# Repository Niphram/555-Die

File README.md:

# 555 Die

Small kit I designed for my brother, may be interesting to some.
Designed using KiCAD 5.

## Parts

| Designator       |               Value |          Package           |
| ---------------- | ------------------: | :------------------------: |
| R13 - R16        |                 1kΩ |       Axial DIN0207        |
| R2, R3, R5 - R12 |                10kΩ |       Axial DIN0207        |
| R1, R4           |               4.7MΩ |       Axial DIN0207        |
| D1 - D7          |                 LED |            5mm             |
| Q1, Q3           |               BC557 |           TO-92            |
| Q2, Q4, Q5       |               BC647 |           TO-92            |
| C1               |               0.1μF | Disc D5.0mm W2.5mm P2.50mm |
| C2               |                 1μF |    Radial D5.0mm P2.5mm    |
| SW1              |         Tact Switch |            6mm             |
| U1               |               NE555 |  DIP-8 (Optional Socket)   |
| U2               |              CD4017 |  DIP-16 (Optional Socket)  |
| BT1              | Powersource (3V-9V) |

> R4 and R1 can be changed to alter timings.

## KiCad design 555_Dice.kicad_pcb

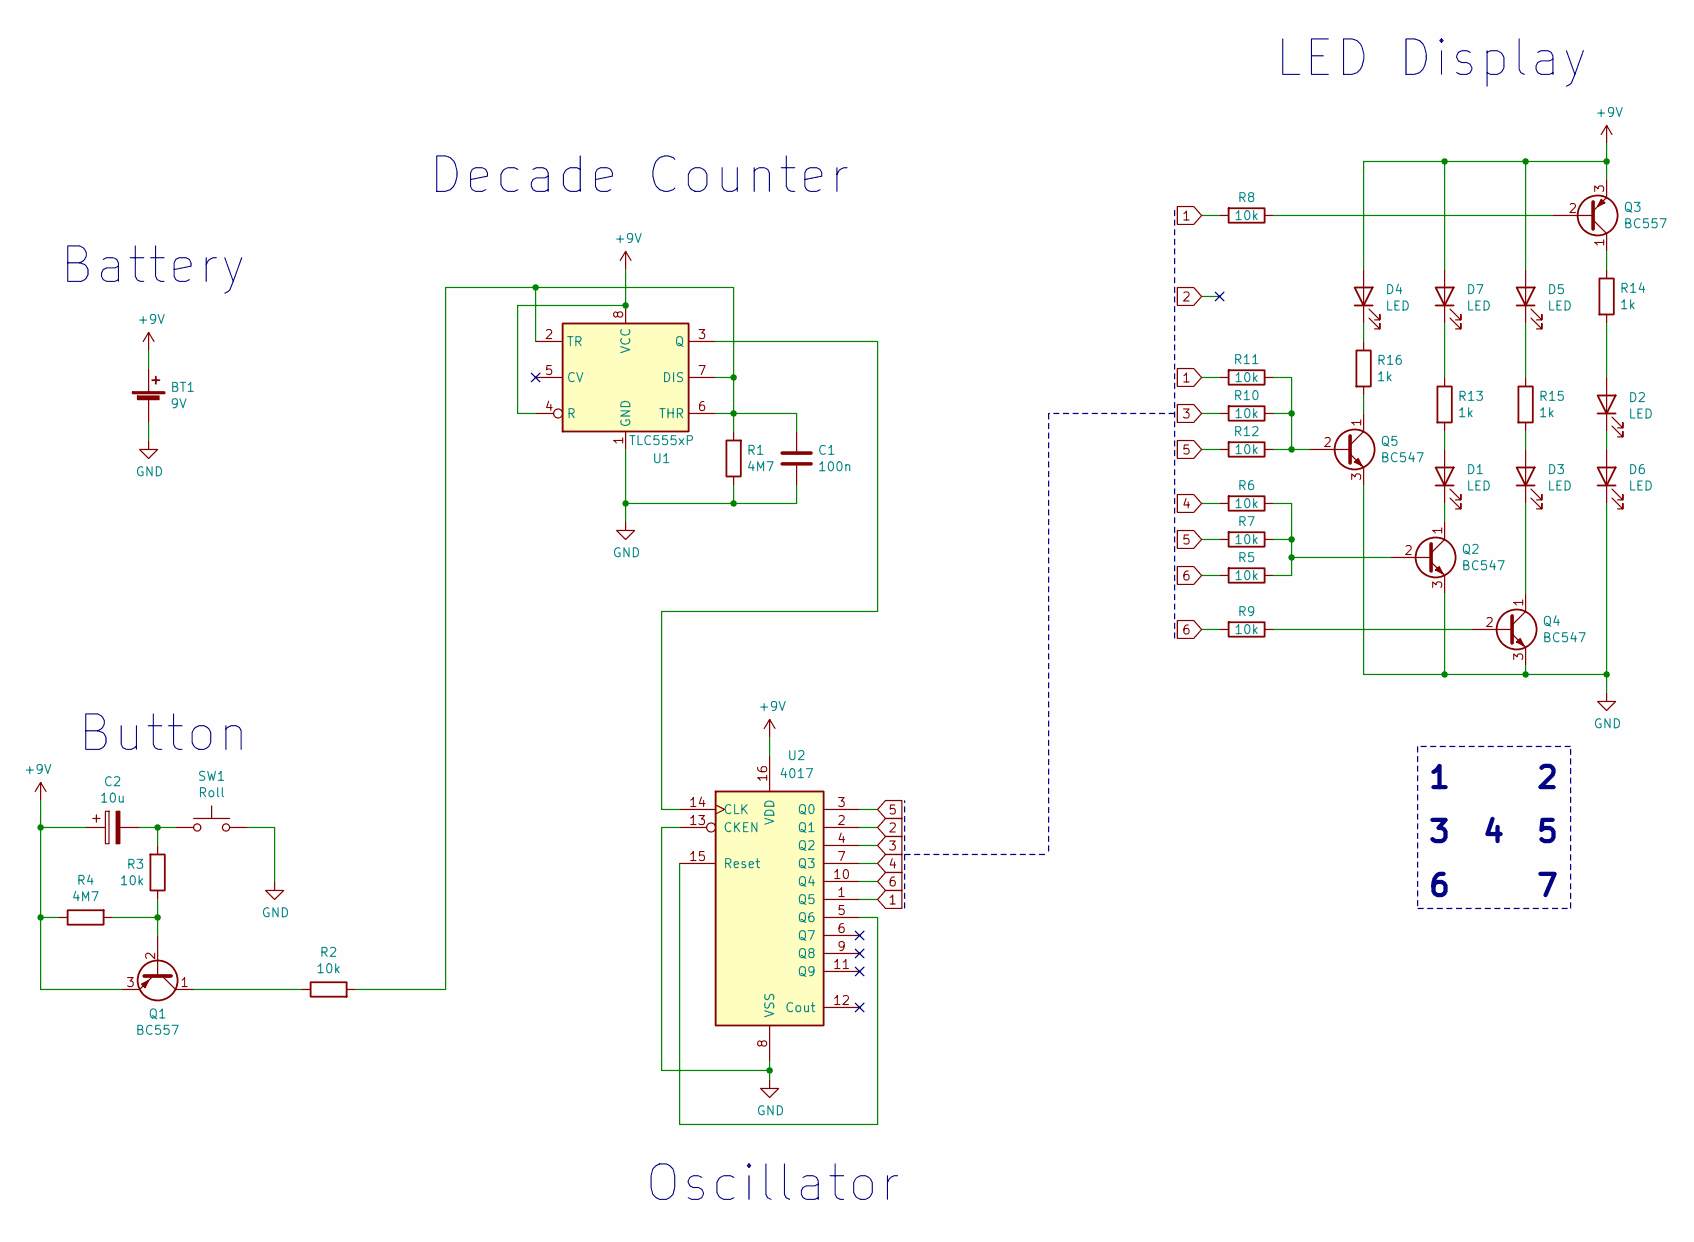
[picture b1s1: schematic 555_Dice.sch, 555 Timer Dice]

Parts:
BT1: 9V; TerminalBlock_bornier-2_P5.08mm
C1: 100n; C_Disc_D5.0mm_W2.5mm_P2.50mm
C2: 10u; CP_Radial_D5.0mm_P2.50mm
D1, D2, D3, D4, D5, D6, D7: LED; LED_D5.0mm
Q1, Q3: BC557; TO-92_HandSolder
Q2, Q4, Q5: BC547; TO-92_HandSolder
R1, R4: 4M7; R_Axial_DIN0207_L6.3mm_D2.5mm_P10.16mm_Horizontal
R2, R3, R5, R6, R7, R8, R9, R10, R11, R12: 10k; R_Axial_DIN0207_L6.3mm_D2.5mm_P10.16mm_Horizontal
R13, R14, R15, R16: 1k; R_Axial_DIN0207_L6.3mm_D2.5mm_P10.16mm_Horizontal
SW1: Roll; SW_PUSH_6mm_H4.3mm
U1: TLC555xP; DIP-8_W7.62mm_Socket_LongPads
U2: 4017; DIP-16_W7.62mm_Socket_LongPads

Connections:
1: R8.2, R11.2, U2.1 (Q5)
2: U2.2 (Q1)
3: R10.2, U2.4 (Q2)
4: R6.2, U2.7 (Q3)
5: R7.2, R12.2, U2.3 (Q0)
6: R5.2, R9.2, U2.10 (Q4)
+9V: BT1.1 (+), C2.1, D4.2 (A), D5.2 (A), D7.2 (A), Q1.3 (E), Q3.3 (E), R4.1, U1.4 (R), U1.8 (VCC), U2.16 (VDD)
GND: BT1.2 (-), C1.2, D6.1 (K), Q2.3 (E), Q4.3 (E), Q5.3 (E), R1.1, SW1.1, U1.1 (GND), U2.8 (VSS), U2.13 (CKEN)
unnamed: C1.1, R1.2, R2.2, U1.2 (TR), U1.6 (THR), U1.7 (DIS)
unnamed: C2.2, R3.2, SW1.2
unnamed: D1.1 (K), Q2.1 (C)
unnamed: D1.2 (A), R13.2
unnamed: D2.1 (K), D6.2 (A)
unnamed: D2.2 (A), R14.2
unnamed: D3.1 (K), Q4.1 (C)
unnamed: D3.2 (A), R15.2
unnamed: D4.1 (K), R16.1
unnamed: D5.1 (K), R15.1
unnamed: D7.1 (K), R13.1
unnamed: Q1.1 (C), R2.1
unnamed: Q1.2 (B), R3.1, R4.2
unnamed: Q2.2 (B), R5.1, R6.1, R7.1
unnamed: Q3.1 (C), R14.1
unnamed: Q3.2 (B), R8.1
unnamed: Q4.2 (B), R9.1
unnamed: Q5.1 (C), R16.2
unnamed: Q5.2 (B), R10.1, R11.1, R12.1
unnamed: U1.3 (Q), U2.14 (CLK)
unnamed: U2.5 (Q6), U2.15 (Reset)

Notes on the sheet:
Battery
Button
Oscillator
Decade Counter
LED Display

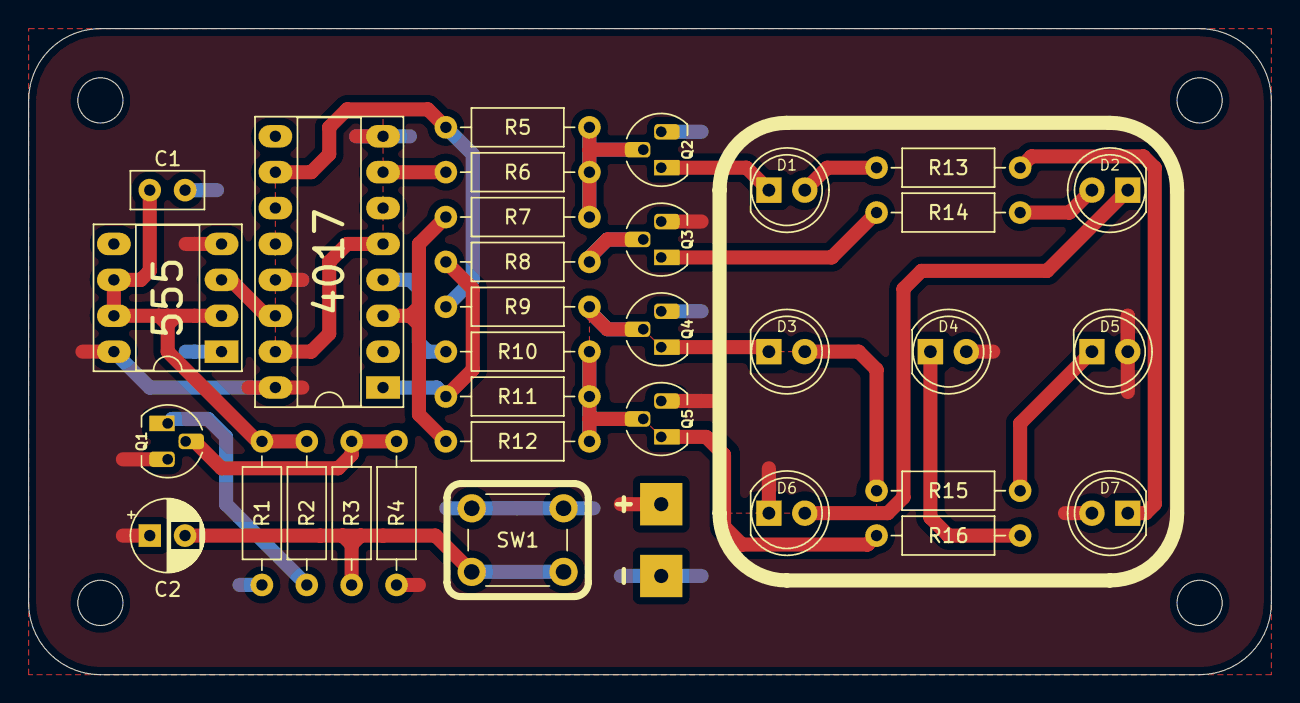
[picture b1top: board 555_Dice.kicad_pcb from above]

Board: 2 copper layers, 87.9 x 45.7 mm, 34 parts (0 on the bottom side), 28 nets.

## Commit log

2021-06-11 Add Readme and License
